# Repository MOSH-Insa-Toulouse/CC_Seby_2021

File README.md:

# Projet Capteur Graphite

Nous vous souhaitons bonne navigation dans notre GitHub ! 

# Sommaire
<!-- TOC depthFrom:2 -->
- [Projet Capteur Graphite](#projet-capteur-graphite)
- [Sommaire](#sommaire)
  - [1. Description](#1-description)
  - [2. Configuration de l'environnement logiciel](#2-configuration-de-lenvironnement-logiciel)
    - [2.1. Arduino](#21-arduino)
      - [2.1.1. Bibliothèques](#211-bibliothèques)
    - [2.2. KICAD](#22-kicad)
    - [2.3. Application Android](#23-application-android)
      - [2.3.1. Installer l'application](#231-installer-lapplication)
      - [2.3.2. Modifier l'application](#232-modifier-lapplication)
  - [3. Améliorations Possibles](#3-améliorations-possibles)
    - [3.1. Amélioration 1 : KICAD - Taille des pistes](#31-amélioration-1--kicad---taille-des-pistes)
    - [3.2. Amélioration 2 : KICAD - Taille des pastilles](#32-amélioration-2--kicad---taille-des-pastilles)
    - [3.3. Amélioration 3 : KICAD - Place du capteur](#33-amélioration-3--kicad---place-du-capteur)
    - [3.4. Amélioration 4 : KICAD - Orientation de l'encodeur rotatoire](#34-amélioration-4--kicad---orientation-de-lencodeur-rotatoire)
    - [3.5. Amélioration 5 : Arduino & Android - Économie du buffer Bluetooth](#35-amélioration-5--arduino--android---économie-du-buffer-bluetooth)
  - [4. Remerciements](#4-remerciements)
  - [5. Informations sur les auteurs](#5-informations-sur-les-auteurs)
<!-- /TOC -->

## 1. Description 

Ce Git contient tous les fichiers requis pour le projet capteur 2021 du Génie Physique de l'INSA de Toulouse.

**Code Arduino**

- Mesure la tension de sortie du circuit transimpédance
- Envoie la mesure de la tension en Bluetooth sur 1 octet
- Calcule la résistance du capteur grâce à l'équation de transfert du circuit dans la data sheet
- Affiche les mesures sur un écran oled 128x32
- Gère l'encodeur rotatoire pour interagir avec un menu sur l'écran oled

**KICAD**

Projet complet de design de shield pour Arduino Uno :

- Interface un module Bluetooth
- Interface un écran oled
- Interface notre capteur graphite via un circuit transimpédance
- Interface un encodeur rotatoire

**Application Android**

- Récupère la mesure de tension en binaire sur 1 octet
- Affiche la valeur de la tension en Volt
- Calcule la résistance du capteur grâce à l'équation de transfert du circuit dans la data sheet
- Affiche la valeur de la résistance MΩ
- Trace un graphique déroulant de la résistance du capteur
- Mise à l'échelle du graphique grâce à un slider

**Data Sheet**

- Caractéristiques principales
- Description du capteur 
- Schéma et dimensions 
- Spécifications
- Conditions d'utilisation normales
- Caractéristiques électriques
- Caractéristiques de déformation
- Montage typique d'utilisation

## 2. Configuration de l'environnement logiciel

### 2.1. Arduino

Lien pour installer l'IDE Arduino sur sa machine : https://www.arduino.cc/en/software

#### 2.1.1. Bibliothèques

À installer depuis l'IDE ou GitHub : 
- Adafruit GFX Library : https://github.com/adafruit/Adafruit-GFX-Library
- Adafruit SSD1306 : https://github.com/adafruit/Adafruit_SSD1306
- Adafruit BusIO : https://github.com/adafruit/Adafruit_BusIO

Comment installer une bibliothèque Arduino ? : https://www.arduino.cc/en/Guide/Libraries#how-to-install-a-library

### 2.2. KICAD

Lien pour installer KICAD sur sa machine : https://www.kicad.org/

### 2.3. Application Android

#### 2.3.1. Installer l'application

Lien pour installer un fichier .apk à partir d'un PC : https://fr.wikihow.com/installer-sur-un-Android-des-fichiers-APK-%C3%A0-partir-d%E2%80%99un-PC

#### 2.3.2. Modifier l'application

Pour modifier le code de l'application Android, vous pouvez utiliser le fichier en .aia dans MIT Inventor : https://appinventor.mit.edu/

## 3. Améliorations Possibles

### 3.1. Amélioration 1 : KICAD - Taille des pistes

À l'INSA Toulouse, la méthode d'impression du Shield par photolithographie avec du matériel rudimentaire a engendré de nombreux court-circuits entre les pistes de la plaque. Il peut-être judicieux d'augmenter la taille des pistes du PCB dans KICAD selon le matériel. **À l'INSA 0.8mm sont recommandés**

**Comment modifier la taille des pistes ?**

Il faut ensuite supprimer les pistes et refaire le routage de la carte.

### 3.2. Amélioration 2 : KICAD - Taille des pastilles

À l'INSA Toulouse, le foret de la perceuse a un diamètre de 0.8mm, il faut donc prévoir un **perçage supérieur ou égal à 0.8mm**.

### 3.3. Amélioration 3 : KICAD - Place du capteur

**Description du problème**

Les pins de connexion fournis du shield à l'Arduino étant un peu courts. Les soudures des connexions du capteur sont en contact avec le boitier de blindage de l'USB qui est à la masse. Nous avons rajouté une feuille de papier entre le Shield et l'Arduino afin d'assurer l'isolation. Un changement de design du Shield serait donc judicieux avant toute nouvelle impression.

**Solution Proposée**

### 3.4. Amélioration 4 : KICAD - Orientation de l'encodeur rotatoire

**Description du problème**

Le bouton poussoir de l'encodeur rotatoire est actuellement orienté vers l'intérieur du shield. La manipulation pourrait être améliorée en orientant l'encodeur vers l'extérieur du shield.

**Solution proposée**

### 3.5. Amélioration 5 : Arduino & Android - Économie du buffer Bluetooth

**Description**

Actuellement, la carte Arduino envoie continuellement les mesures de tension dans le buffer du Bluetooth peu importe qu'un appareil soit connecté ou pas. Le buffer du dongle Bluetooth est alors rempli de vieilles mesures qui seront quand même lues lorsqu'un appareil se mettra à lire les données.

**Solution Proposée**

_Arduino_

- Création d'une variable Mode_Bluetooth de type entier 
- Création d'une procédure de modification de Mode_Bluetooth lors de la réception de strings particuliers en Bluetooth
- Ajout d'un bloc If Mode_Bluetooth qui conditionne l'envoi des mesures en Bluetooth

_Android_

- Envoi d'un string en Bluetooth (ex : "ON") lorsqu'on démarre le timer de mesure
- Envoi d'un string en Bluetooth (ex : "OFF") lorsqu'on arrête le timer de mesure

## 4. Remerciements

Nous tenons à remercier toutes les personnes qui nous ont aidé tout au long de ce projet !

## 5. Informations sur les auteurs

**Séléna PONDARD**

Étudiante en 4ème année du Génie Physique de l'INSA de Toulouse

Mail : pondard@etud.insa-toulouse.fr

**Sébastien LENI**

Étudiant en 4ème année du Génie Physique de l'INSA de Toulouse

Mail : leni@etud.insa-toulouse.fr

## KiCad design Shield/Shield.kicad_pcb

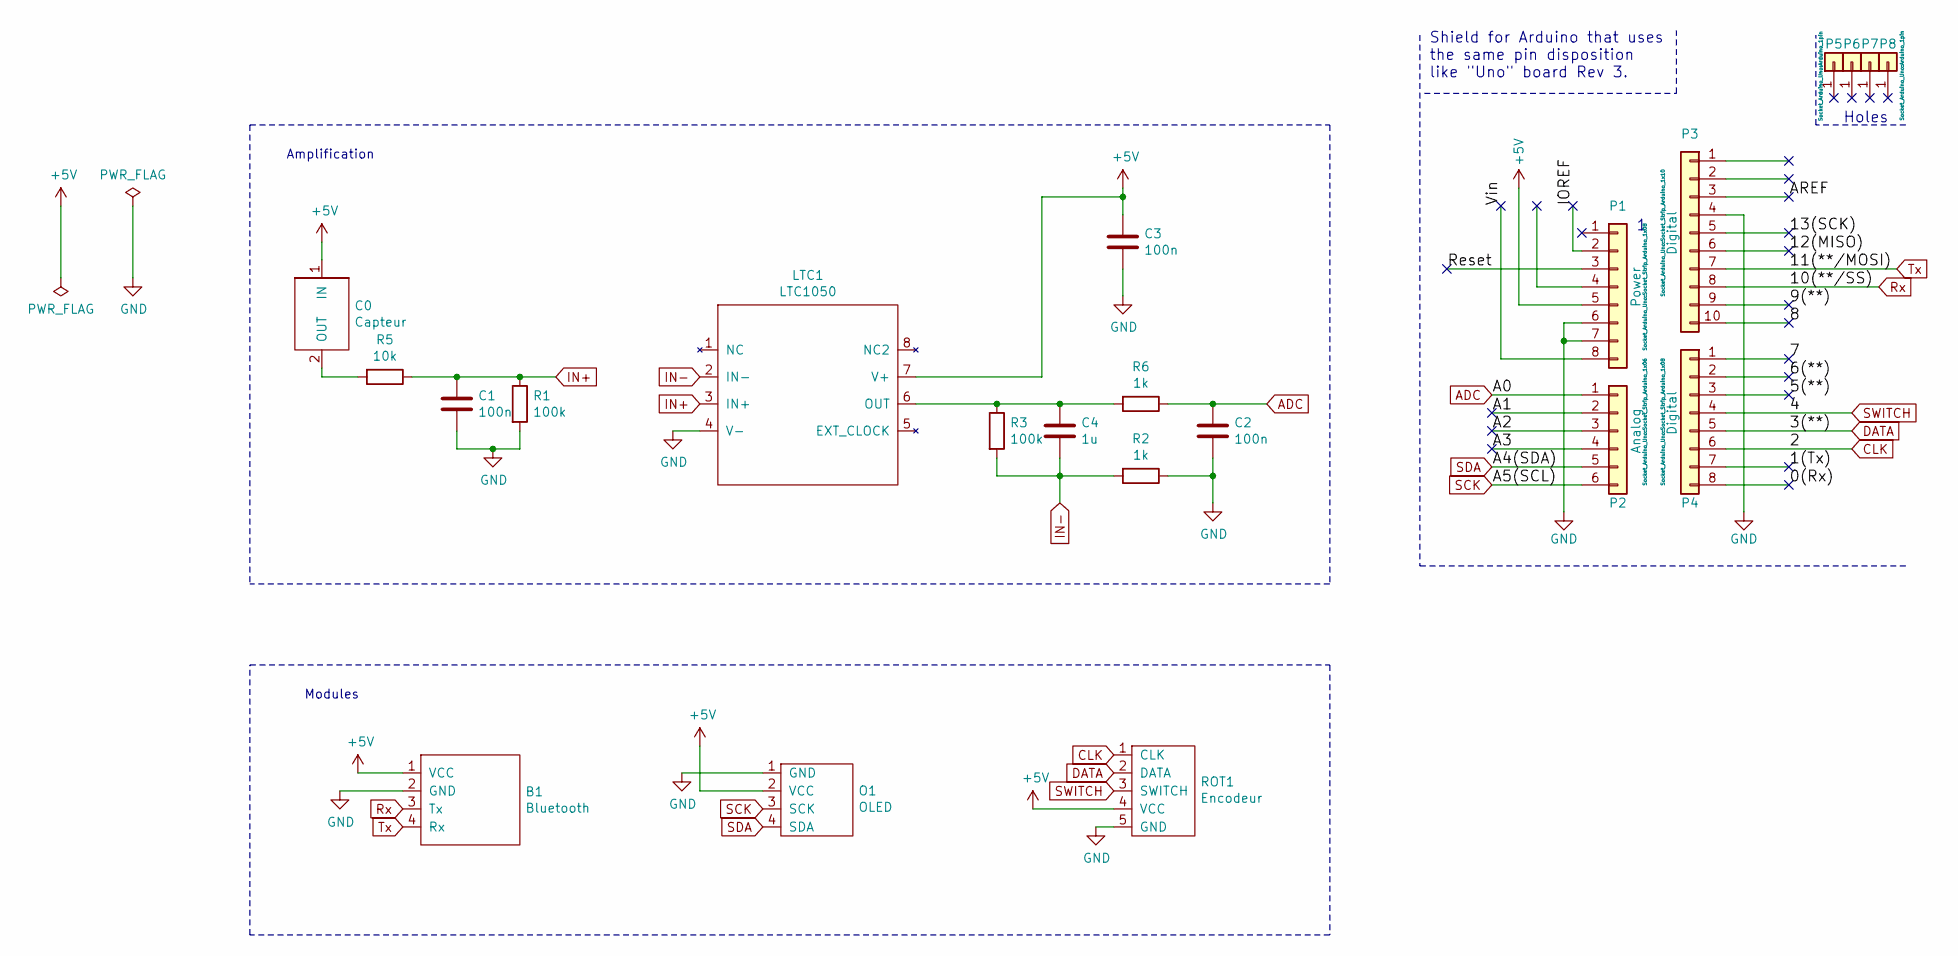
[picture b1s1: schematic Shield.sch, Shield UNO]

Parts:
B1: Bluetooth
C0: Capteur
C1, C2, C3: 100n; C_Axial_L3.8mm_D2.6mm_P7.50mm_Horizontal
C4: 1u; C_Rect_L7.0mm_W6.0mm_P5.00mm
LTC1: LTC1050
O1: OLED
P1: Power; Socket_Strip_Arduino_1x08
P2: Analog; Socket_Strip_Arduino_1x06
P3: Digital; Socket_Strip_Arduino_1x10
P4: Digital; Socket_Strip_Arduino_1x08
P5, P6, P7, P8: CONN_01X01; Arduino_1pin
R1, R3: 100k; R_Axial_DIN0204_L3.6mm_D1.6mm_P5.08mm_Horizontal
R2, R6: 1k; R_Axial_DIN0204_L3.6mm_D1.6mm_P5.08mm_Horizontal
R5: 10k; R_Axial_DIN0204_L3.6mm_D1.6mm_P5.08mm_Horizontal
ROT1: Encodeur

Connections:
+5V: B1.1 (VCC), C0.1 (IN), C3.1, LTC1.7 (V+), O1.2 (VCC), P1.5, ROT1.4 (VCC)
/0(Rx): P4.8
/1(Tx): P4.7
/5(**): P4.3
/6(**): P4.2
/7: P4.1
/8: P3.10
/9(**): P3.9
/12(MISO): P3.6
/13(SCK): P3.5
/A1: P2.2
/A2: P2.3
/A3: P2.4
/AREF: P3.3
/IOREF: P1.2
/Reset: P1.3
/Vin: P1.8
ADC: C2.1, P2.1, R6.1
CLK: P4.6, ROT1.1 (CLK)
DATA: P4.5, ROT1.2 (DATA)
GND: B1.2 (GND), C1.2, C2.2, C3.2, LTC1.4 (V-), O1.1 (GND), P1.6, P1.7, P3.4, R1.2, R2.1, ROT1.5 (GND)
IN+: C1.1, LTC1.3 (IN+), R1.1, R5.1
IN-: C4.2, LTC1.2 (IN-), R2.2, R3.2
unnamed: C0.2 (OUT), R5.2
unnamed: C4.1, LTC1.6 (OUT), R3.1, R6.2
Rx: B1.3 (Tx), P3.8
SCK: O1.3 (SCK), P2.6
SDA: O1.4 (SDA), P2.5
SWITCH: P4.4, ROT1.3 (SWITCH)
Tx: B1.4 (Rx), P3.7

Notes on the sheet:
Holes
Shield for Arduino that uses the same pin disposition like "Uno" board Rev 3.
Amplification
Modules

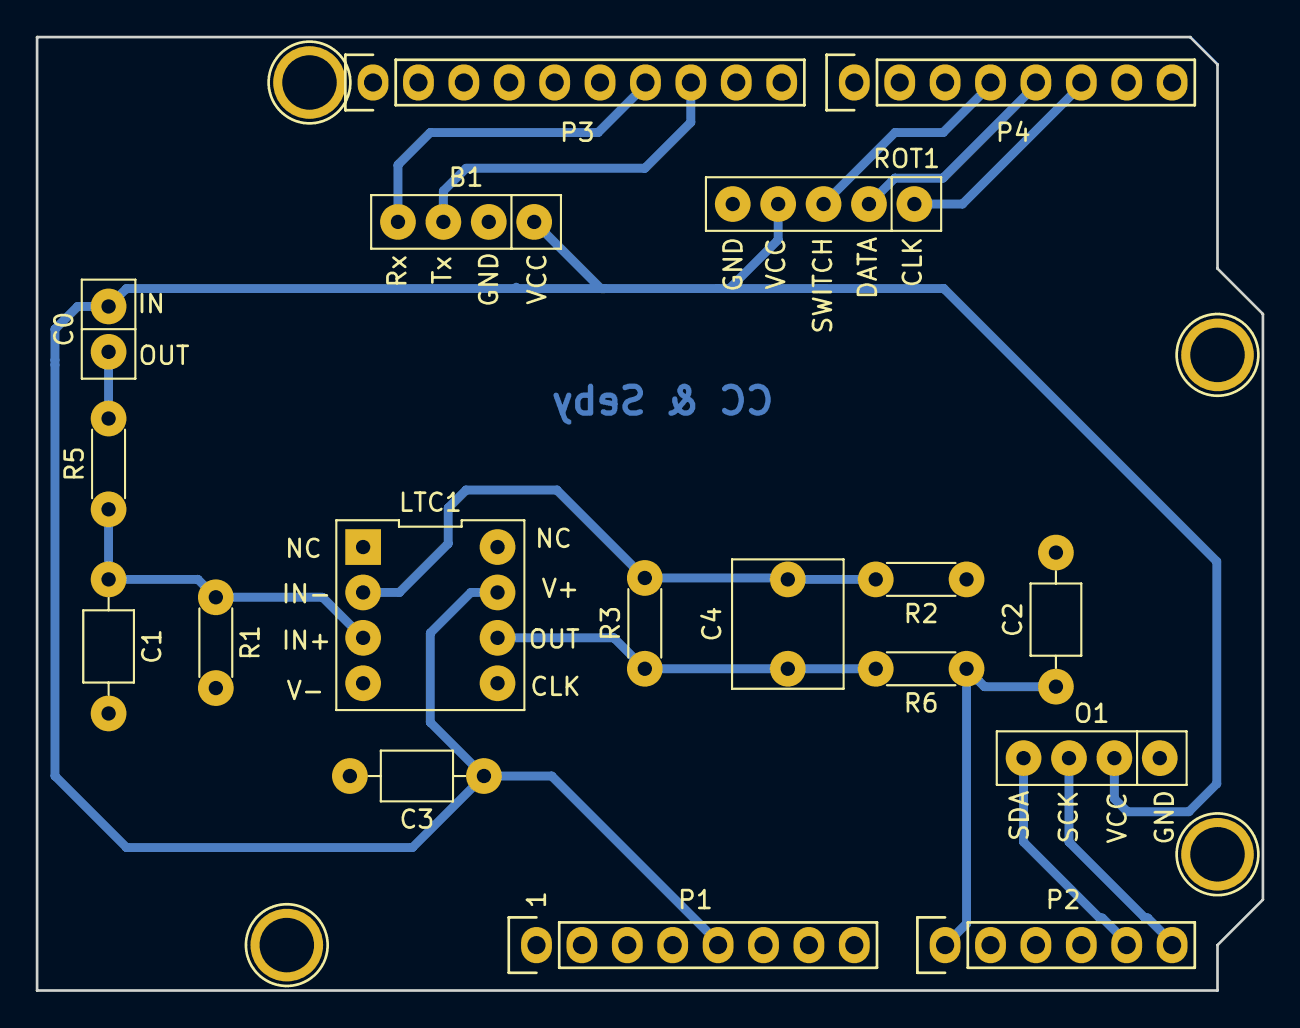
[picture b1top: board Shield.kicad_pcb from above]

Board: 2 copper layers, 68.6 x 53.3 mm, 22 parts (0 on the bottom side), 14 nets.

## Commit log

2021-02-05 test
2021-02-05 test2
2021-02-05 DebutProjet
2021-02-23 Code Arduino V0
2021-03-05 KICAD
2021-03-05 ARDUINO V2
2021-03-08 Datasheet V0
2021-03-08 Datasheet V0.1
2021-03-08 Arduino MAJ
2021-03-10 cc a reussi
2021-03-10 modification Arduino
2021-03-16 Début datasheet
2021-03-17 Ca marche
2021-03-18 ca roule
2021-03-18 Shield qui marche
2021-03-21 Avancée Datasheet
2021-03-23 read1
2021-03-23 readme
2021-03-23 Il est trop tard
2021-03-24 Fichier pour impression
2021-03-25 banc de test
2021-03-25 Readme du futur
2021-03-25 j'en ai marre
2021-03-26 Ptn de démo
2021-03-26 datasheiz
2021-03-27 correction graphique
2021-03-28 Git du dimanche soir
2021-04-09 ca sent la fin
2021-04-09 Ca sent la fin pour de vrai
2021-04-10 Gin Schweppes
2021-04-28 The end CC
2021-04-29 the end Seby
2021-05-05 Et ça repart
2021-05-17 on est de retour
2021-05-21 Sommaire
